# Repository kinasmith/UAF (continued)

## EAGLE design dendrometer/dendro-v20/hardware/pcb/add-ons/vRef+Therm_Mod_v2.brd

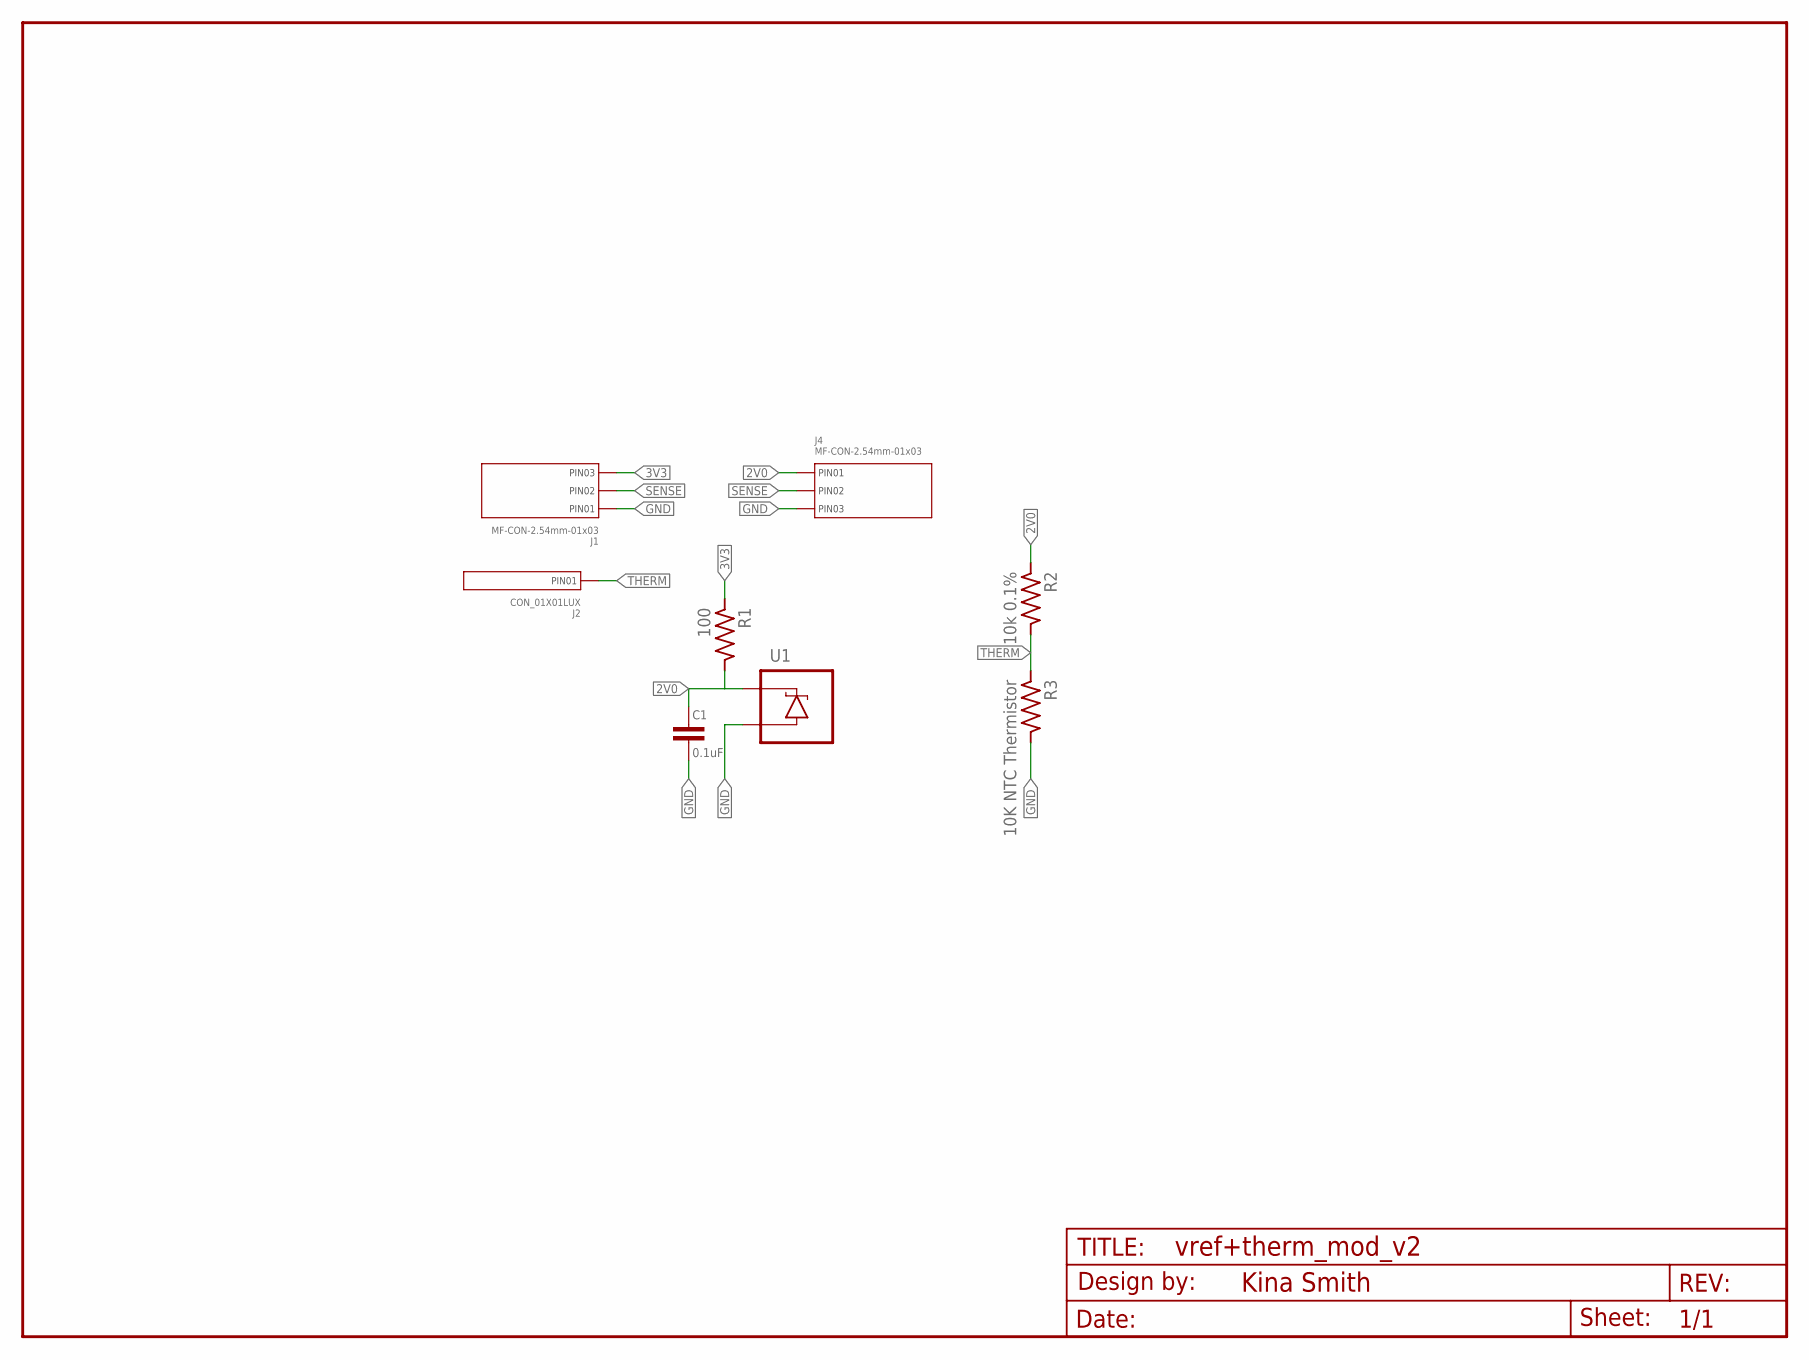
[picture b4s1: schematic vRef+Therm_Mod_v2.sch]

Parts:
C1: 0.1uF; C0603-N
FRAME1: FRAME-LETTERNO_PACKAGE; DUMMY
J1, J4: MF-CON-2.54mm-01x03; PTH_2.54MM_01X03
J2: CON_01X01LUX; 1X01_LUXEON-PAD
R1: 100; R0603-N
R2: 10k 0.1%; R0603-N
R3: 10K NTC Thermistor; R0603-N
U1: LM4040-SOT-23-3; SOT23-3

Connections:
2V0: C1.1, J4.P$1 (PIN1), R1.2, R2.1, U1.1 (C)
3V3: J1.P$3 (PIN3), R1.1
GND: C1.2, J1.P$1 (PIN1), J4.P$3 (PIN3), R3.2, U1.2 (A)
SENSE: J1.P$2 (PIN2), J4.P$2 (PIN2)
THERM: J2.P$1, R2.2, R3.1

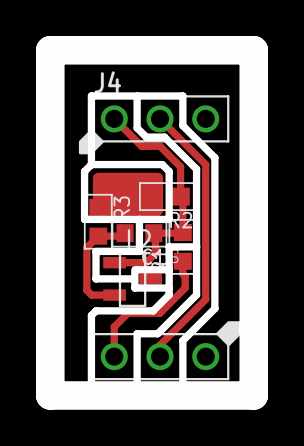
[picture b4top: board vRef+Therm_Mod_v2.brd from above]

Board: 2 copper layers, 11.3 x 19.2 mm, 9 parts (0 on the bottom side), 5 nets.

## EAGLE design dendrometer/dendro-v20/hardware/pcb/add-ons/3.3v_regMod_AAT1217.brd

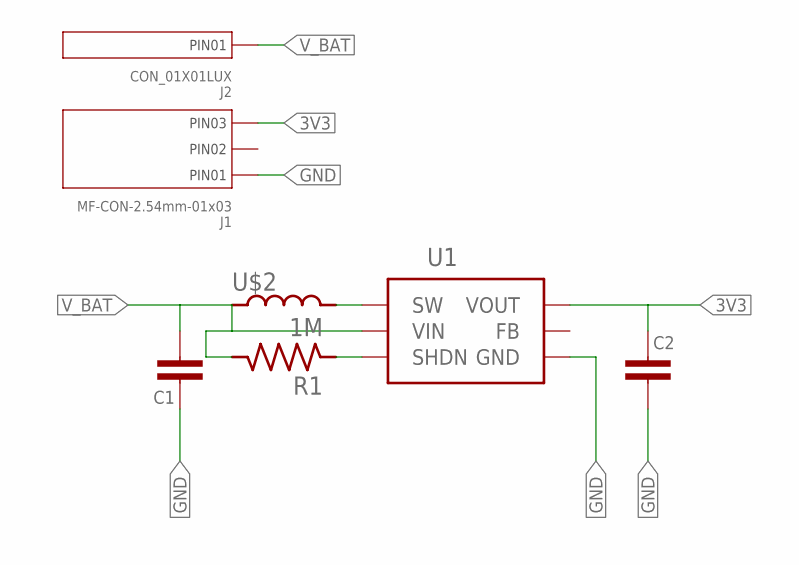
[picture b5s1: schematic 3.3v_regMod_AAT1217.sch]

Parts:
C1, C2: CAPACITOR_NP0603-N; C0603-N
J1: MF-CON-2.54mm-01x03; PTH_2.54MM_01X03
J2: CON_01X01LUX; 1X01_LUXEON-PAD
R1: 1M; R0603-N
U1: AAT1217-SOT23-6; SOT23-6
U$2: INDUCTOR3030; L3030

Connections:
3V3: C2.1, J1.P$3 (PIN3), U1.5 (VOUT)
GND: C1.1, C2.2, J1.P$1 (PIN1), U1.2 (GND)
unnamed: U1.1 (SW), U$2.P$2
unnamed: R1.1, U1.4 (SHDN)
V_BAT: C1.2, J2.P$1, R1.2, U1.6 (VIN), U$2.P$1

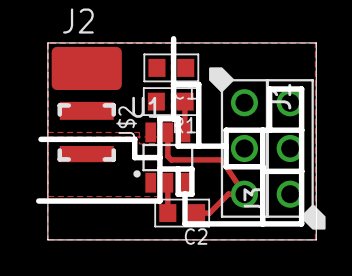
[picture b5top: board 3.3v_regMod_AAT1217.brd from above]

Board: 2 copper layers, 15.3 x 11.0 mm, 8 parts (0 on the bottom side), 5 nets.

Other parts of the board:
J3: MF-CON-2.54mm-01x03; PTH_2.54MM_01X03

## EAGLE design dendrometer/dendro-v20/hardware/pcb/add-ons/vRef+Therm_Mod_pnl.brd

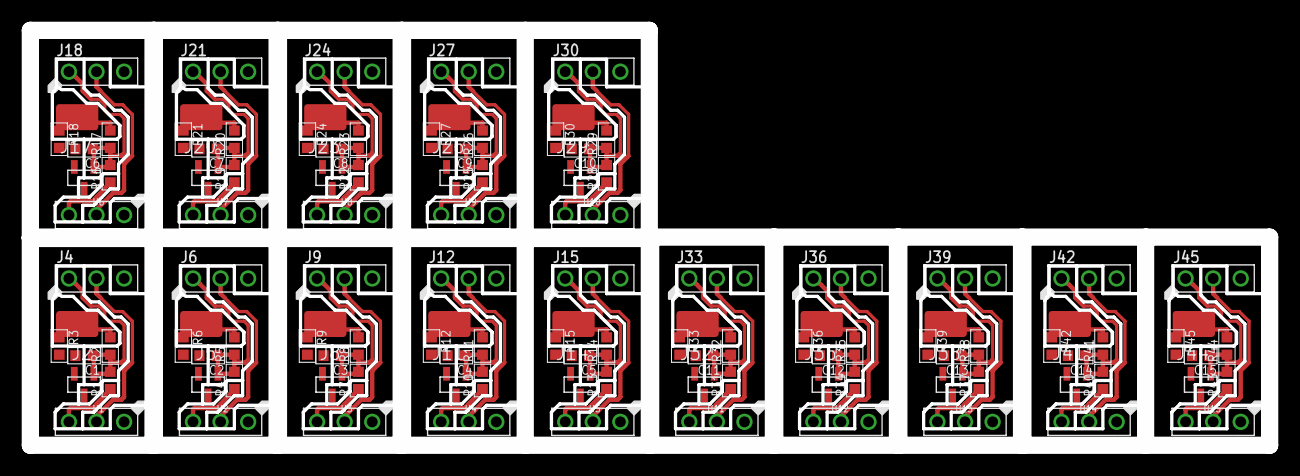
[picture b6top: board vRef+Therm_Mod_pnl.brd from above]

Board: 2 copper layers, 114.2 x 38.2 mm, 120 parts (0 on the bottom side), 75 nets.

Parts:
C1, C2, C3, C4, C5, C6, C7, C8, C9, C10, C11, C12, C13, C14, C15: 0.1uF; C0603-N
J1, J3, J4, J6, J7, J9, J10, J12, J13, J15, J16, J18, J19, J21, J22, J24, J25, J27, J28, J30, J31, J33, J34, J36, J37, J39, J40, J42, J43, J45: MF-CON-2.54mm-01x03; PTH_2.54MM_01X03
J2, J5, J8, J11, J14, J17, J20, J23, J26, J29, J32, J35, J38, J41, J44: CON_01X01LUX; 1X01_LUXEON-PAD
R1, R4, R7, R10, R13, R16, R19, R22, R25, R28, R31, R34, R37, R40, R43: 100; R0603-N
R2, R5, R8, R11, R14, R17, R20, R23, R26, R29, R32, R35, R38, R41, R44: 10k 0.1%; R0603-N
R3, R6, R9, R12, R15, R18, R21, R24, R27, R30, R33, R36, R39, R42, R45: 10K NTC Thermistor; R0603-N
U1, U2, U3, U4, U5, U6, U7, U8, U9, U10, U11, U12, U13, U14, U15: LM4040-SOT-23-3; SOT23-3

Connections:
2V0: C1.1, J4.P$1, R1.2, R2.1, U1.1
2V1: C2.1, J6.P$1, R4.2, R5.1, U2.1
2V2: C3.1, J9.P$1, R7.2, R8.1, U3.1
2V3: C4.1, J12.P$1, R10.2, R11.1, U4.1
2V4: C5.1, J15.P$1, R13.2, R14.1, U5.1
2V5: C6.1, J18.P$1, R16.2, R17.1, U6.1
2V6: C7.1, J21.P$1, R19.2, R20.1, U7.1
2V7: C8.1, J24.P$1, R22.2, R23.1, U8.1
2V8: C9.1, J27.P$1, R25.2, R26.1, U9.1
2V9: C10.1, J30.P$1, R28.2, R29.1, U10.1
2V10: C11.1, J33.P$1, R31.2, R32.1, U11.1
2V11: C12.1, J36.P$1, R34.2, R35.1, U12.1
2V12: C13.1, J39.P$1, R37.2, R38.1, U13.1
2V13: C14.1, J42.P$1, R40.2, R41.1, U14.1
2V14: C15.1, J45.P$1, R43.2, R44.1, U15.1
3V1: J3.P$3, R4.1
3V2: J7.P$3, R7.1
3V3: J1.P$3, R1.1
3V4: J10.P$3, R10.1
3V5: J13.P$3, R13.1
3V6: J16.P$3, R16.1
3V7: J19.P$3, R19.1
3V8: J22.P$3, R22.1
3V9: J25.P$3, R25.1
3V10: J28.P$3, R28.1
3V11: J31.P$3, R31.1
3V12: J34.P$3, R34.1
3V13: J37.P$3, R37.1
3V14: J40.P$3, R40.1
3V15: J43.P$3, R43.1
GND: C1.2, J1.P$1, J4.P$3, R3.2, U1.2
GND1: C2.2, J3.P$1, J6.P$3, R6.2, U2.2
GND2: C3.2, J7.P$1, J9.P$3, R9.2, U3.2
GND3: C4.2, J10.P$1, J12.P$3, R12.2, U4.2
GND4: C5.2, J13.P$1, J15.P$3, R15.2, U5.2
GND5: C6.2, J16.P$1, J18.P$3, R18.2, U6.2
GND6: C7.2, J19.P$1, J21.P$3, R21.2, U7.2
GND7: C8.2, J22.P$1, J24.P$3, R24.2, U8.2
GND8: C9.2, J25.P$1, J27.P$3, R27.2, U9.2
GND9: C10.2, J28.P$1, J30.P$3, R30.2, U10.2
GND10: C11.2, J31.P$1, J33.P$3, R33.2, U11.2
GND11: C12.2, J34.P$1, J36.P$3, R36.2, U12.2
GND12: C13.2, J37.P$1, J39.P$3, R39.2, U13.2
GND13: C14.2, J40.P$1, J42.P$3, R42.2, U14.2
GND14: C15.2, J43.P$1, J45.P$3, R45.2, U15.2
SENSE: J1.P$2, J4.P$2
SENSE1: J3.P$2, J6.P$2
SENSE2: J7.P$2, J9.P$2
SENSE3: J10.P$2, J12.P$2
SENSE4: J13.P$2, J15.P$2
SENSE5: J16.P$2, J18.P$2
SENSE6: J19.P$2, J21.P$2
SENSE7: J22.P$2, J24.P$2
SENSE8: J25.P$2, J27.P$2
SENSE9: J28.P$2, J30.P$2
SENSE10: J31.P$2, J33.P$2
SENSE11: J34.P$2, J36.P$2
SENSE12: J37.P$2, J39.P$2
SENSE13: J40.P$2, J42.P$2
SENSE14: J43.P$2, J45.P$2
THERM: J2.P$1, R2.2, R3.1
THERM1: J5.P$1, R5.2, R6.1
THERM2: J8.P$1, R8.2, R9.1
THERM3: J11.P$1, R11.2, R12.1
THERM4: J14.P$1, R14.2, R15.1
THERM5: J17.P$1, R17.2, R18.1
THERM6: J20.P$1, R20.2, R21.1
THERM7: J23.P$1, R23.2, R24.1
THERM8: J26.P$1, R26.2, R27.1
THERM9: J29.P$1, R29.2, R30.1
THERM10: J32.P$1, R32.2, R33.1
THERM11: J35.P$1, R35.2, R36.1
THERM12: J38.P$1, R38.2, R39.1
THERM13: J41.P$1, R41.2, R42.1
THERM14: J44.P$1, R44.2, R45.1

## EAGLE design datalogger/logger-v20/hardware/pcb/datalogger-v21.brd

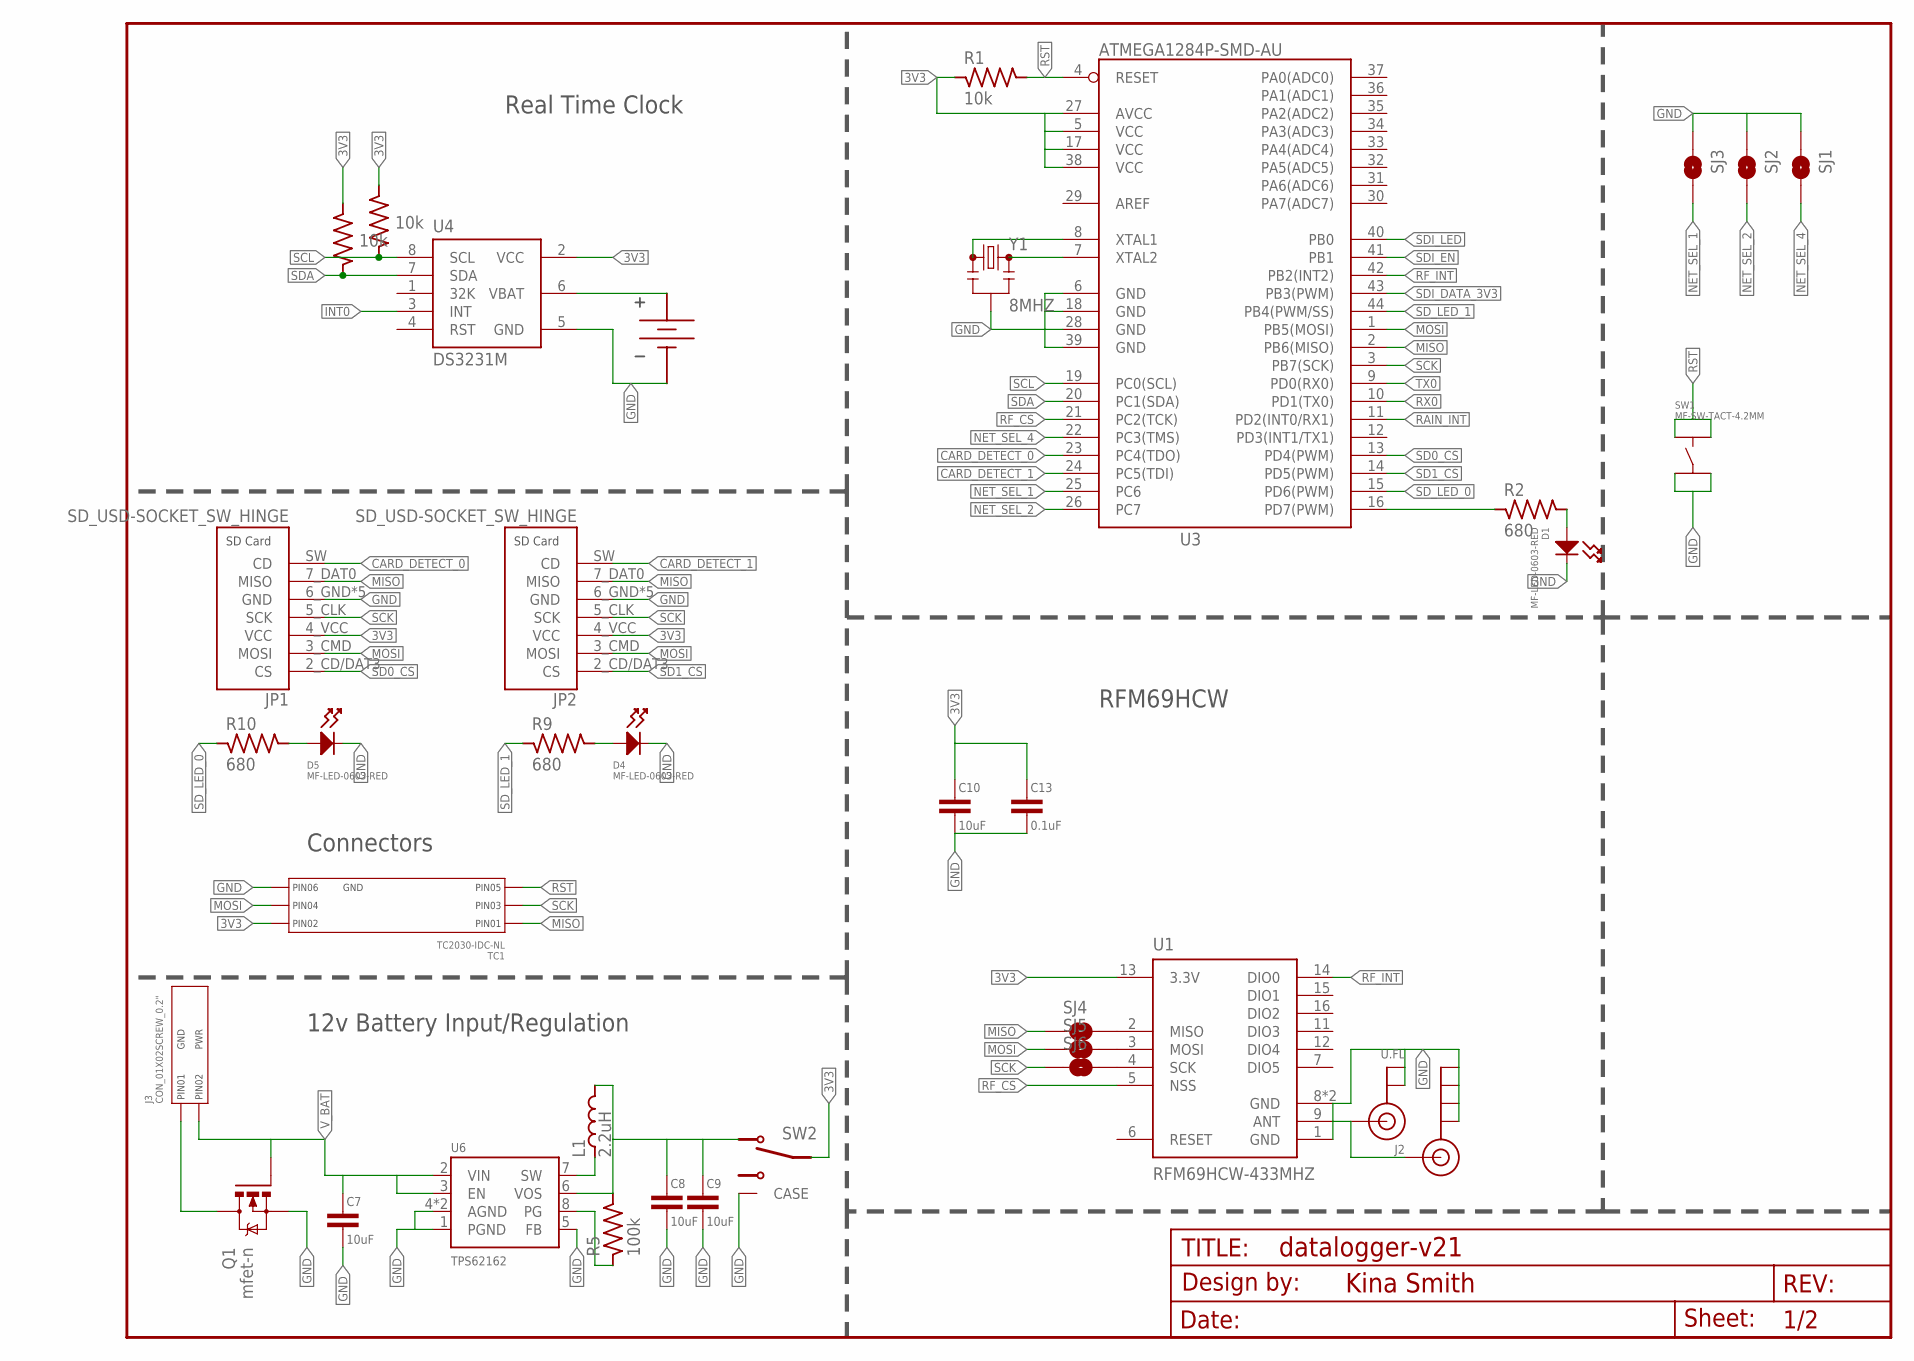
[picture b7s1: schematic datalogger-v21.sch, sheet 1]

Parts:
BAT1: BATTERY_HOLDER12MM; BAT_12MM
C7, C8, C9, C10: 10uF; C0805-N; PARTNO GRM21BR61C106KE15L
C13: 0.1uF; C0603-N; PARTNO CC0603KRX7R7BB104
D1, D4, D5: MF-LED-0603-RED; LED0603
FRAME1: FRAME-LETTERNO_PACKAGE; DUMMY
J2: U.FL; ADAFRUIT_U.FL
J3: CON_01X02SCREW_0.2"; SCREW_TERM_2POS
J4: ANTENNA_SMA_EDGE; SMA-EDGE
JP1, JP2: SD_USD-SOCKET_SW_HINGE; SD_MICRO_HIROSE-DM3C
L1: 2.2uH; L2520; PARTNO VLS252012T-2R2M1R3
Q1: mfet-n; SOT23-3; PARTNO SI2312BDS-T1-GE3
R1, R3, R4: 10k; R0603-N; PARTNO RC0603FR-0710KL
R2, R9, R10: 680; R0603-N; PARTNO RC0603FR-0710KL
R5: 100k; R0603-N; PARTNO RC0603FR-07100KL
SJ1, SJ2, SJ3, SJ4, SJ5, SJ6: JUMPER-PAD-2-NOYES_SILK; PAD-JUMPER-2-NO_YES_SILK
SW1: MF-SW-TACT-4.2MM; TACT4.2MM
SW2: SWITCH_SPDT_SMD_ES01MSABE; SPDT_ES01MSABE
TC1: TC2030-IDC-NL; PARTNO NA
U1: RFM69HCW-433MHZ; RFM69HCW-XXXS2
U3: ATMEGA1284P-SMD-AU; TQFP44
U4: DS3231M; SO08
U6: TPS62162; WSON-8
Y1: 8MHZ; RESONATOR-SMD

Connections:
3V3: C10.1, C13.1, JP1.4_VCC (VCC), JP2.4_VCC (VCC), R1.1, R3.2, R4.2, SW2.2 (COM), TC1.P$2 (PIN2), U1.13 (3.3V), U3.5 (VCC), U3.17 (VCC), U3.27 (AVCC), U3.38 (VCC), U4.2 (VCC); also elsewhere on the board
3V3_PRE: C8.1, C9.1, L1.P$2, R5.2, SW2.1, U6.6 (VOS); also elsewhere on the board
ANT: J2.3 (SIGNAL), J4.SIG (SIGNAL), U1.9 (ANT)
CARD_DETECT_0: JP1.SW (CD), U3.23 (PC4(TDO))
CARD_DETECT_1: JP2.SW (CD), U3.24 (PC5(TDI))
GND: BAT1.GND, C7.2, C8.2, C9.2, C10.2, C13.2, D1.CATHODE, D4.CATHODE, D5.CATHODE, J2.1 (GND), J2.2 (GND), J4.GND@0 (GND), J4.GND@1 (GND), J4.GND@2 (GND), J4.GND@3 (GND), JP1.6_GND (GND), JP1.GND1 (GND), JP1.GND2 (GND), JP1.GND3 (GND), JP1.GND4 (GND), JP2.6_GND (GND), JP2.GND1 (GND), JP2.GND2 (GND), JP2.GND3 (GND), JP2.GND4 (GND), Q1.2 (S), SJ1.1, SJ2.1, SJ3.1, SW1.P$3, SW1.P$4, SW2.GND (CASE), SW2.GND1 (CASE), TC1.P$6 (PIN6), U1.1 (GND), U1.8 (GND), U1.10 (GND), U3.6 (GND), U3.18 (GND), U3.28 (GND), U3.39 (GND), U4.5 (GND), U6.1 (PGND), U6.4 (AGND), U6.5 (FB), U6.P$9 (AGND), Y1.2; also elsewhere on the board
INT0: U4.3 (INT)
MISO: JP1.7_DAT0 (MISO), JP2.7_DAT0 (MISO), SJ4.1, TC1.P$1 (PIN1), U3.2 (PB6(MISO))
MOSI: JP1.3_CMD (MOSI), JP2.3_CMD (MOSI), SJ5.1, TC1.P$4 (PIN4), U3.1 (PB5(MOSI))
unnamed: J3.GND (PIN1), Q1.3 (D)
unnamed: R2.1, U3.16 (PD7(PWM))
unnamed: U3.7 (XTAL2), Y1.3
unnamed: D4.ANODE, R9.2
unnamed: U3.8 (XTAL1), Y1.1
unnamed: L1.P$1, U6.7 (SW)
unnamed: SJ4.2, U1.2 (MISO)
unnamed: D1.ANODE, R2.2
unnamed: SJ5.2, U1.3 (MOSI)
unnamed: BAT1.PWR@1 (VBAT), BAT1.PWR@2 (VBAT), U4.6 (VBAT)
unnamed: R5.1, U6.8 (PG)
unnamed: SJ6.2, U1.4 (SCK)
unnamed: D5.ANODE, R10.2
NET_SEL_1: SJ3.2, U3.25 (PC6)
NET_SEL_2: SJ2.2, U3.26 (PC7)
NET_SEL_4: SJ1.2, U3.22 (PC3(TMS))
RAIN_INT: U3.11 (PD2(INT0/RX1)); also elsewhere on the board
RF_CS: U1.5 (NSS), U3.21 (PC2(TCK))
RF_INT: U1.14 (DIO0), U3.42 (PB2(INT2))
RST: R1.2, SW1.P$1, SW1.P$2, TC1.P$5 (PIN5), U3.4 (RESET); also elsewhere on the board
RX0: U3.10 (PD1(TX0)); also elsewhere on the board
SCK: JP1.5_CLK (SCK), JP2.5_CLK (SCK), SJ6.1, TC1.P$3 (PIN3), U3.3 (PB7(SCK))
SCL: R3.1, U3.19 (PC0(SCL)), U4.8 (SCL)
SD0_CS: JP1.2_CD/DAT3 (CS), U3.13 (PD4(PWM))
SD1_CS: JP2.2_CD/DAT3 (CS), U3.14 (PD5(PWM))
SDA: R4.1, U3.20 (PC1(SDA)), U4.7 (SDA)
SDI_DATA_3V3: U3.43 (PB3(PWM)); also elsewhere on the board
SDI_EN: U3.41 (PB1); also elsewhere on the board
SDI_LED: U3.40 (PB0); also elsewhere on the board
SD_LED_0: R10.1, U3.15 (PD6(PWM))
SD_LED_1: R9.1, U3.44 (PB4(PWM/SS))
TX0: U3.9 (PD0(RX0)); also elsewhere on the board
V_BAT: C7.1, J3.PWR (PIN2), Q1.1 (G), U6.2 (VIN), U6.3 (EN); also elsewhere on the board

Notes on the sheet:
12v Battery Input/Regulation
RFM69HCW
Connectors
Real Time Clock

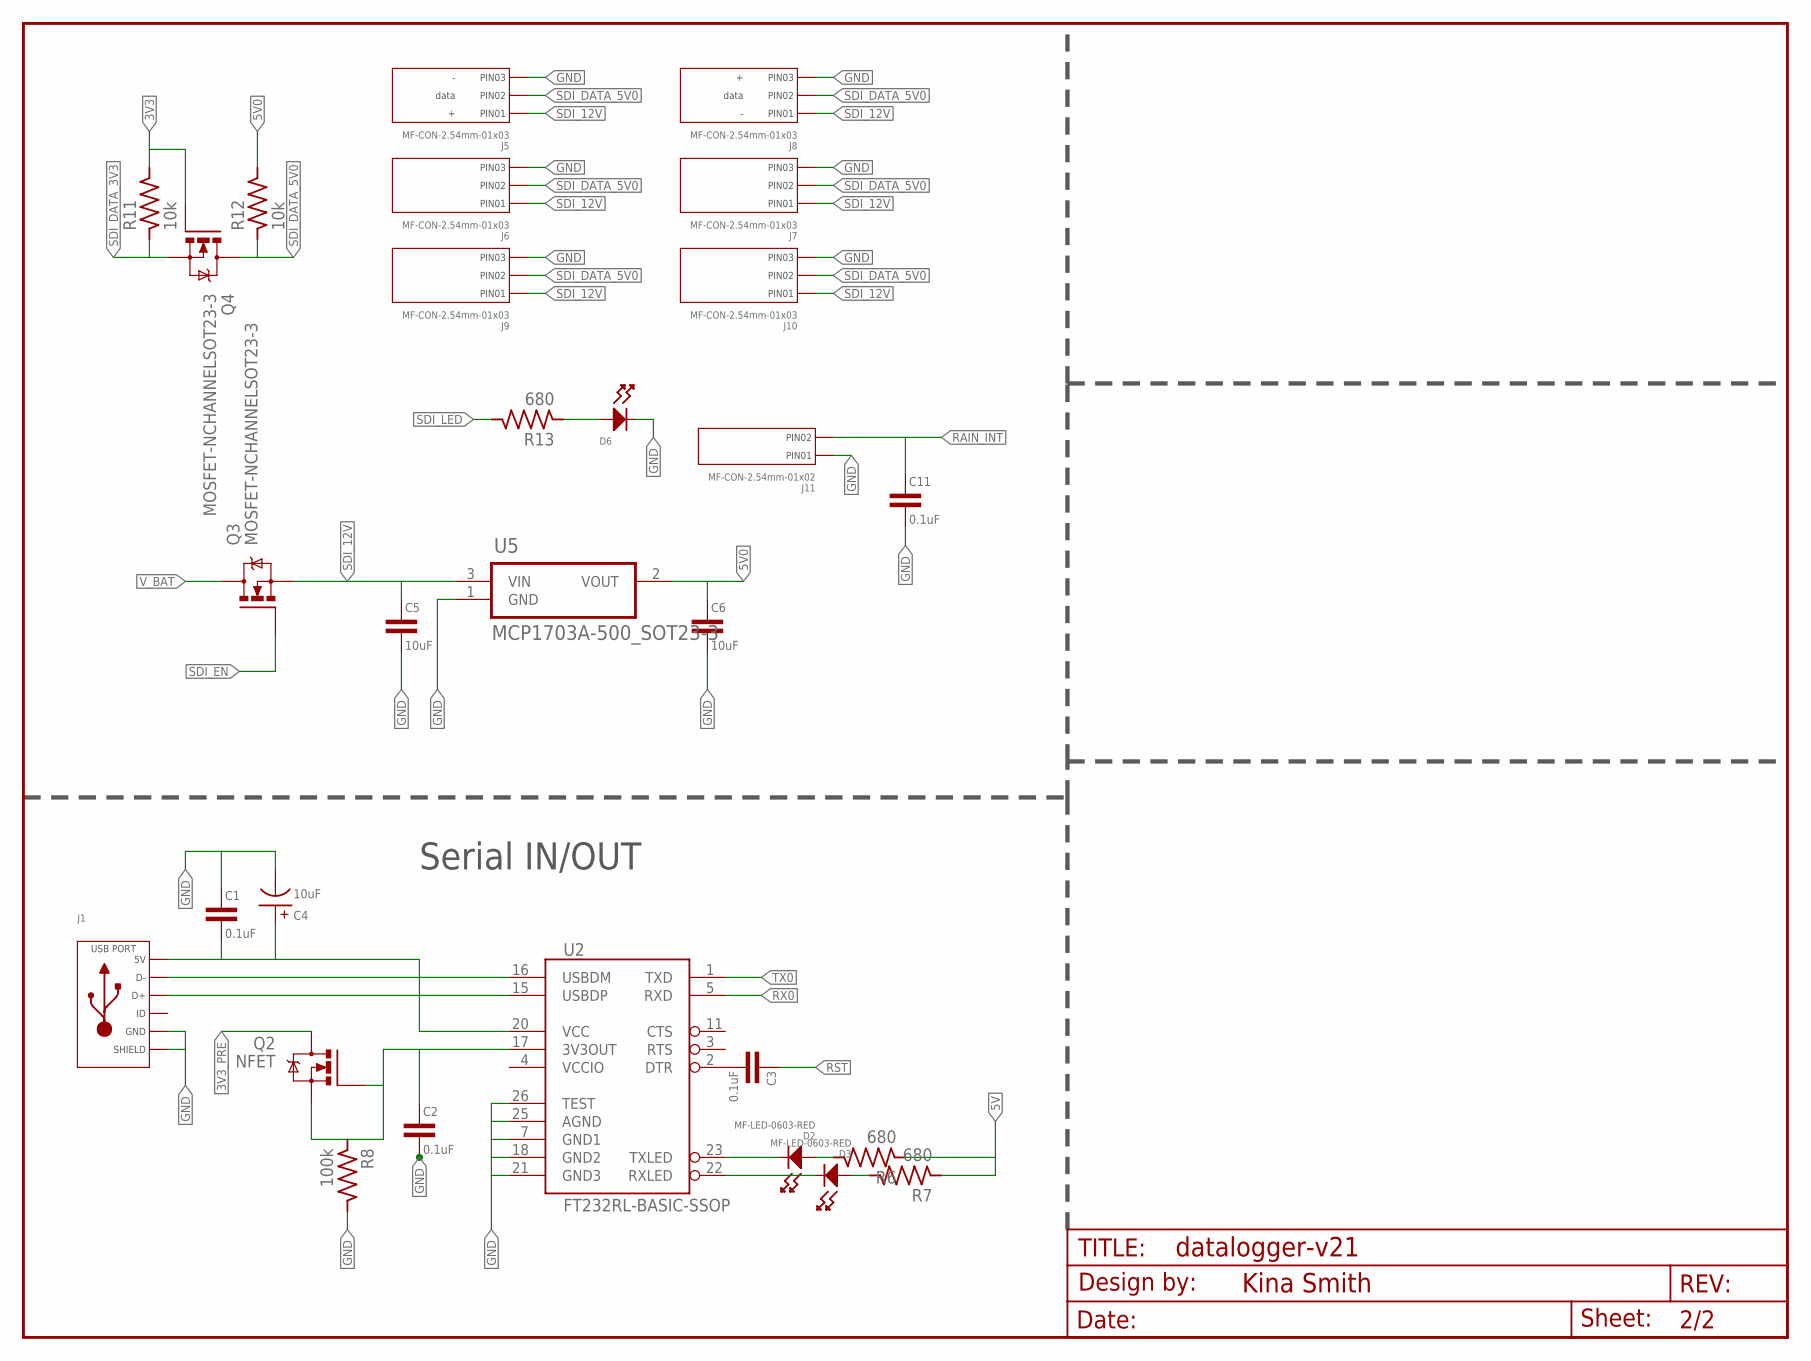
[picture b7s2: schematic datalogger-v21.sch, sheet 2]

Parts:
C1, C2, C3, C11: 0.1uF; C0603-N
C4: 10uF; EIA3216
C5, C6: 10uF; C0805-N
D2, D3: MF-LED-0603-RED; LED0603
D6: LED_SINGLE-0603; LED0603
FRAME3: FRAME-LETTERNO_PACKAGE; DUMMY
J1: USB-5PIN_B-MICRO_R/A_STRONG; USB-MICRO-MOLEX-105017-0001
J5, J6, J7, J8, J9, J10: MF-CON-2.54mm-01x03; PTH_2.54MM_01X03
J11: MF-CON-2.54mm-01x02; PTH_2.54MM_01X02
Q2: NFET; SOT23-3
Q3, Q4: MOSFET-NCHANNELSOT23-3; SOT23-3
R6, R7, R13: 680; R0603-N
R8: 100k; R0603-N
R11, R12: 10k; R0603-N
U2: FT232RL-BASIC-SSOP; SSOP28
U5: MCP1703A-500_SOT23-3; SOT23-3

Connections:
3V3: Q4.1 (G), R11.2; also elsewhere on the board
3V3_PRE: Q2.3 (D); also elsewhere on the board
5V: C1.2, C4.A (POS), J1.1 (5V), R6.1, R7.1, U2.20 (VCC)
5V0: C6.1, R12.2, U5.2 (VOUT)
GND: C1.1, C2.2, C4.C (NEG), C5.2, C6.2, C11.2, D6.CATHODE, J1.5 (GND), J1.P$1 (SLD), J1.P$2 (SLD), J1.P$3 (SLD), J1.P$4 (SLD), J1.P$5 (SLD), J1.P$6 (SLD), J5.P$3 (PIN3), J6.P$3 (PIN3), J7.P$3 (PIN3), J8.P$3 (PIN3), J9.P$3 (PIN3), J10.P$3 (PIN3), J11.P$1 (PIN1), R8.2, U2.7 (GND1), U2.18 (GND2), U2.21 (GND3), U2.25 (AGND), U2.26 (TEST), U5.1 (GND); also elsewhere on the board
unnamed: J1.2 (D-), U2.16 (USBDM)
unnamed: J1.3 (D+), U2.15 (USBDP)
unnamed: D6.ANODE, R13.1
unnamed: C2.1, Q2.1 (G), Q2.2 (S), R8.1, U2.17 (3V3OUT)
unnamed: C3.2, U2.2 (DTR)
unnamed: D2.CATHODE, U2.23 (TXLED)
unnamed: D3.CATHODE, U2.22 (RXLED)
unnamed: D3.ANODE, R7.2
unnamed: D2.ANODE, R6.2
RAIN_INT: C11.1, J11.P$2 (PIN2); also elsewhere on the board
RST: C3.1; also elsewhere on the board
RX0: U2.5 (RXD); also elsewhere on the board
SDI_12V: C5.1, J5.P$1 (PIN1), J6.P$1 (PIN1), J7.P$1 (PIN1), J8.P$1 (PIN1), J9.P$1 (PIN1), J10.P$1 (PIN1), Q3.2 (S), U5.3 (VIN)
SDI_DATA_3V3: Q4.2 (S), R11.1; also elsewhere on the board
SDI_DATA_5V0: J5.P$2 (PIN2), J6.P$2 (PIN2), J7.P$2 (PIN2), J8.P$2 (PIN2), J9.P$2 (PIN2), J10.P$2 (PIN2), Q4.3 (D), R12.1
SDI_EN: Q3.1 (G); also elsewhere on the board
SDI_LED: R13.2; also elsewhere on the board
TX0: U2.1 (TXD); also elsewhere on the board
VCCIO: U2.4 (VCCIO)
V_BAT: Q3.3 (D); also elsewhere on the board

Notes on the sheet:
Serial IN/OUT

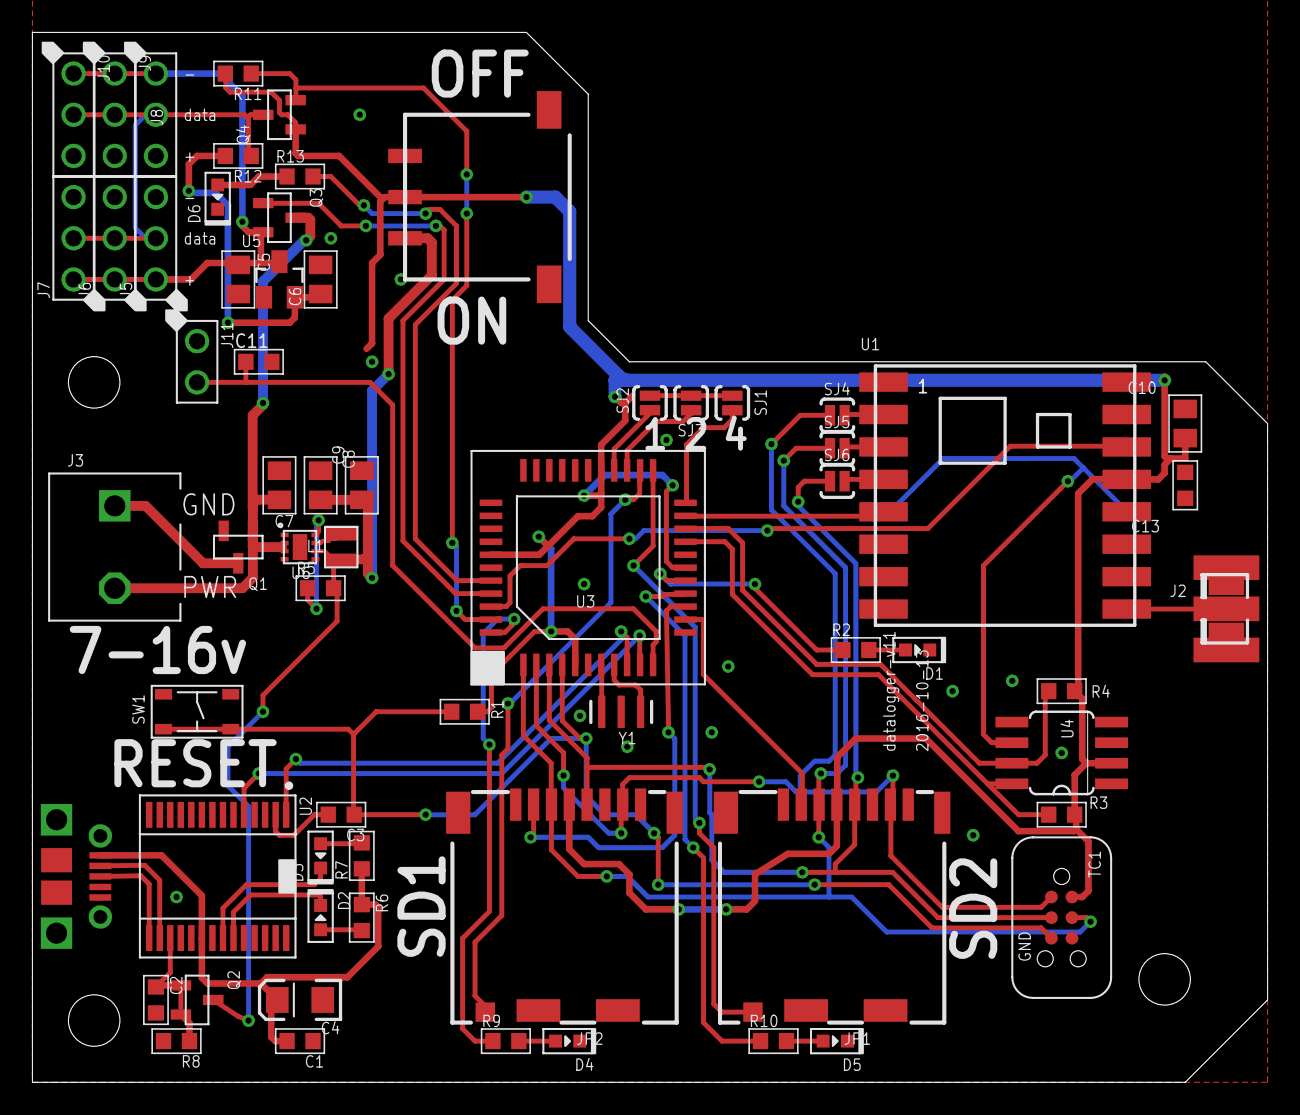
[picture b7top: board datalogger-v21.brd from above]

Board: 2 copper layers, 76.2 x 64.8 mm, 68 parts (1 on the bottom side), 54 nets.

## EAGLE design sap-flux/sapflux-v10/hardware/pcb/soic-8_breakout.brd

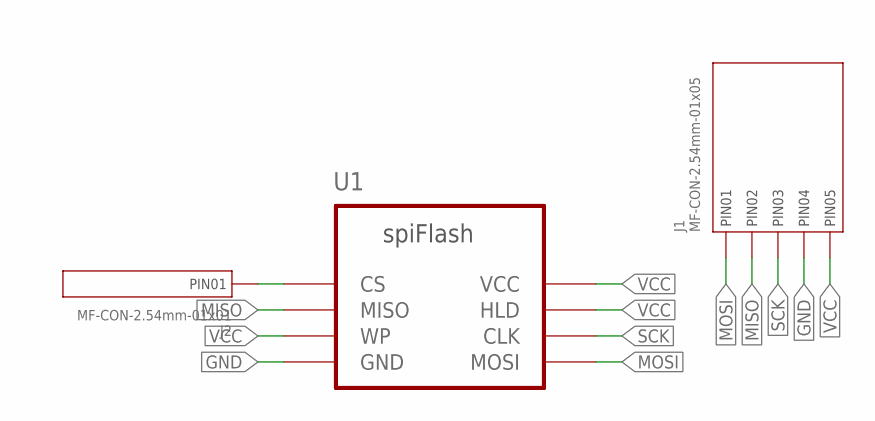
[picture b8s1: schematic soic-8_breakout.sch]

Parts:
J1: MF-CON-2.54mm-01x05; PTH_2.54MM_01X05
J2: MF-CON-2.54mm-01x01; PTH_2.54MM_01X01
U1: WINBOND_FLASH_4MBIT-SOIC; SOIC8

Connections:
GND: J1.P$4 (PIN4), U1.4 (GND)
MISO: J1.P$2 (PIN2), U1.2 (MISO)
MOSI: J1.P$1 (PIN1), U1.5 (MOSI)
unnamed: J2.P$1, U1.1 (CS)
SCK: J1.P$3 (PIN3), U1.6 (CLK)
VCC: J1.P$5 (PIN5), U1.3 (WP), U1.7 (HLD), U1.8 (VCC)

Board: 2 copper layers, 3 parts (0 on the bottom side), 6 nets, no tracks yet.

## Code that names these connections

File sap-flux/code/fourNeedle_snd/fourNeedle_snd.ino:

/*
   Tc 1: CSpin 9
   Tc 2: CSpin 8
   Tc 3: CSpin 7
   Tc Heat: CSpin 6
   H_en: pin 5
*/

#include <SPI.h>
#include "RFM69.h"
#include "Adafruit_MAX31855.h"

#define NODE_ID         2
#define NETWORK_ID      105
#define GATEWAY_ID      0
#define FREQUENCY       RF69_433MHZ
#define KEY             "p6ZNvTmGfdY2hUXb" //has to be same 16 characters/bytes on all nodes, not more not less!
#define ACK_TIME        100  // # of ms to wait for an ack
#define NB_ATTEMPTS_ACK 5 //number of attempts to try before giving up

#define Tc1_CS 9
#define Tc2_CS 8
#define Tc3_CS 7
#define TcH_CS 6
#define H_en 5

Adafruit_MAX31855 Tc1(Tc1_CS);
Adafruit_MAX31855 Tc2(Tc2_CS);
Adafruit_MAX31855 Tc3(Tc3_CS);
Adafruit_MAX31855 TcH(TcH_CS);
RFM69 radio;

long TRANSMIT_PERIOD = 30000; //transmit a packet to gateway so often (in ms)
int TRANSMIT_PERIOD_MINUTES = 1;
int ACK_FAIL_WAIT_PERIOD = 500;


long currentTime;
long h_saved_time;
long h_interval;
const long h_pulse_on = 6000;
const long h_pulse_off = 30 * 60000;
//const long h_pulse_off = 60000;
int h_status = 1;

long log_saved_time;
int log_interval = 6000;

typedef struct {
  int node_id;
  float Tc1_t;
  float Tc2_t;
  float Tc3_t;
  float TcH_t;
}
Payload;
Payload payload;

void setup() {
  Serial.begin(9600);
  pinMode(H_en, OUTPUT);
  digitalWrite(H_en, LOW);
payload.node_id = NODE_ID;
  radio.initialize(FREQUENCY, NODE_ID, NETWORK_ID); //Begin Radio
  radio.setHighPower(); //uncomment only for RFM69HW!
  radio.encrypt(KEY); //Encrypt
  radio.sleep(); //Sleep radio (saves power)
  char buff[50];
  sprintf(buff, "Listening at %d Mhz...", FREQUENCY == RF69_433MHZ ? 433 : FREQUENCY == RF69_868MHZ ? 868 : 915);
}

void loop() {
  currentTime = millis();
  if (h_saved_time + h_interval < currentTime) {
    //if heater is on, wait 6 seconds
    if (h_status == 1) {
      digitalWrite(H_en, HIGH);
      h_interval = h_pulse_on;
      h_status = 0; //set status for next round.
      Serial.print("Heat interval ");
      Serial.print(h_pulse_on / 1000);
      Serial.println("s");
    }
    else if (h_status == 0) {
      digitalWrite(H_en, LOW);
      h_interval = h_pulse_off;
      h_status = 1; //set status for next round
      Serial.print("Heat interval ");
      Serial.print(h_pulse_off / 1000);
      Serial.println("s");
    }
    h_saved_time = currentTime;
  }
  if (log_saved_time + log_interval < currentTime) {
    payload.Tc1_t = Tc1.readCelsius();
    payload.Tc2_t = Tc2.readCelsius();
    payload.Tc3_t = Tc3.readCelsius();
    payload.TcH_t = TcH.readCelsius();
    sendPacket();
    printPacket();
    log_saved_time = currentTime;
  }
}

void sendPacket() {
  int nAttempt = 0; 
  bool flag_ACK_received = false;
  while (nAttempt < NB_ATTEMPTS_ACK && !flag_ACK_received) { 
    if (radio.sendWithRetry(GATEWAY_ID, (const void*)(&payload), sizeof(payload))) { 
      flag_ACK_received = true;
    }
    else { 
      if (radio.sendWithRetry(GATEWAY_ID, (const void*)(&payload), sizeof(payload))) {
        flag_ACK_received = true; 
      }
      nAttempt++;
      ACK_FAIL_WAIT_PERIOD = random(300, 600);
      delay(ACK_FAIL_WAIT_PERIOD);
    }
  }
}
void printPacket() {
  Serial.print(payload.Tc1_t);
  Serial.print(", ");
  Serial.print(payload.Tc2_t);
  Serial.print(", ");
  Serial.print(payload.Tc3_t);
  Serial.print(", ");
  Serial.print(payload.TcH_t);
  Serial.println();
}

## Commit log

2016-03-07 added ignore file
2016-03-07 global .gitignore didn't work..hmm
2016-03-07 added folders and BOM's
2016-03-07 moved stuff around, ready to work
2016-03-07 added libraries folder
2016-03-07 added project timeline
2016-03-08 added datasheets, ds3231 breakout pcb, got test code for senders and receiver. test writing to SD card overnight to test stability.
2016-03-09 started the mechanical design in SLDWRKS
2016-03-09 changed the test sketches. Recording tempreading from RFM69 radio and bat. voltage. Initiating longer term test. Also data from overnight random number test
2016-03-09 added bolt tabs to dendrometer housing.
2016-03-10 did some more stuff to the solidworks files...I forgot what
2016-03-16 moved SD card write to correct place in code to fix double writes
2016-03-16 did some minor pcb work and did some data analysis
2016-03-16 changed where it was writing to SD card. Fixed duplicate writes
2016-04-05 I've been way behind. Here is a shitload of stuff. Status is, everything is working pretty darn well right now
2016-04-07 made .brd for pcb fab house. and other minor code changes
2016-04-13 generated gerber files and did some minor mech. work
2016-04-15 did minor stuff mostly. However created Reciever_0 and added SD card checking
2016-04-29 bunch of shit. oops
2016-06-13 ....long time. bunch of stuff...oops
2016-06-13 added debug Serial Print logic, modified the RTC library on RCV.
2016-06-13 switched to SDfat library and changed the SD fail interaction
2016-06-13 staged for deployment
2016-06-13 final upload...
2016-07-21 cleanup..
2016-08-23 massive move and restructure
2016-08-23 move in of all other projects
2016-08-23 dummy...wtf electron
2016-08-23 added electron folder to ignore
2016-08-23 moved welder files into subdir
2016-08-24 minor code updates...
2016-08-24 updated Sender_ and removed Serial.prints
2016-08-25 changed some things
2016-09-07 added particle stuff and made a breakout for rfm69hcw
2016-09-08 test data and new breakout board for themocouple amp
2016-09-08 changed
2016-09-30 crazy long time since I did this. hah
2016-10-10 added datasheets, test data, etc
2016-10-10 datalogger pcb design
2016-11-09 again....this is stupid
2016-11-11 two way communication. time stamp to sndr boards. and flow chart
2016-11-11 local data storage. auto send backed up data. And it works
2016-11-19 working on storing/transmitting data from sensors. Might have a working system by moving all send events out of the receive event. Needs further testing.
2016-11-23 Sap Flux Schematic. New parts in Eagle Libs. Block Diagram of Sap Flux system
2016-12-13 sap flux BOM, Gerbers, Radiation Shield Files
2016-12-14 removed optiboot
2016-12-28 started Dendro-v60
2017-01-03 massive shift. Moving to PlatformIO as an IDE
2017-01-03 testing git plugin
2017-01-03 changed formatting slightly.
2017-01-18 new circuit board. testing components
2017-01-18 battery voltage working...something weird with it now though
2017-01-18 something wrong with the SPI Bus
2017-01-19 spiflash memory
2017-01-19 Flash AND Radio works!
2017-01-20 talking to radio and flash mem. Need more testing for data storage and retrieval, but in testing it works to manually save/delete/retrieve data
2017-01-20 code variant for Sap Flux system with small v11 datalogger board
2017-01-20 cleanup
2017-01-20 added a junk folder
2017-01-20 working on flash mem. Try simple examples on how to save data repeatedly in the same locations
2017-01-24 flash mem. storage is working. Next steps: routines for flux measurements
2017-01-24 flash works with this code....going to move in sensor reading blocks
2017-01-24 also everything is FUCKED
2017-01-24 everything is STILL FUCKED
2017-01-25 still not fucked
2017-01-25 trying something that will FUCK IT UP
2017-01-25 not fucked yet
2017-01-25 not fucked....what the fuck
2017-01-25 this fucked everything
2017-01-25 FUCKING WORKS
2017-01-25 Fucked again
2017-01-25 things are working like a charm. Next, figure out how to seperate data chunks when re-transmitting
2017-01-25 changed payload uint16_t's to doubles to allow for Floats
2017-01-25 working for the most part, for now
2017-01-25 minor tweak for saving values.
2017-01-26 made datalogger latching
2017-01-26 logger now latches to sensor during data transmission. Needs testing
2017-01-30 Kind of fucked up the libraries and no things are not responding due to new MAX31856 Library
2017-01-30 MAX31856 library works, but now Flash is broken
2017-01-30 changed library thingy
2017-01-30 testing my MAX31856 Library
2017-01-31 works, but only when reset without the FTDI installed
2017-01-31 over night test
2017-01-31 Got the correct time stamp behavior working with reading back storage data
2017-01-31 just set the time and commented out the TIME SETTING thing
2017-01-31 minor stuff for overnight test
2017-01-31 nothing
2017-01-31 fixed readme
2017-02-03 added test data
2017-02-03 Data from field site. and worked on pcb slightly
2017-02-07 working on updating code and building add-on mods for system
2017-02-07 new dendro datalogger code. Based off home automation, and sap flux dev
2017-02-07 just nothing
2017-02-07 forgot to save
2017-02-07 starting power testing
2017-02-07 did power calculations
2017-02-08 final for test
2017-02-08 new data from overnight test
2017-02-09 zipped Data from field sites
2017-02-09 checked all part numbers. Minor modifications to bottom text layer
2017-02-10 created Gerbers
2017-02-10 new test data
2017-02-10 updated bottom Silk Screen
2017-02-11 serial log from overnight test. also notes for debuggin
2017-02-15 testing SDI-12 and Interrupt Rain Bucket. + new Data
2017-02-16 rebuilt model. Tightened tolerances for fit. etc
2017-02-16 made new gerbers including drill file
2017-02-17 changed power Testing code for testing new module
2017-02-17 fixed timing bug and reformed the comms structure so it makes more sense
2017-02-17 added a ping function and tided up some stuff
2017-02-20 fixed initial ping in Setup. ++new data
2017-02-21 small changes to datalogger
2017-02-28 added data
2017-02-28 making add-on boards for dendro upgrades)
2017-03-01 updated dendro logger code. fixed the latch ID variable type. was int changed to uint
2017-03-01 updating
2017-03-02 getting the dendro's ready to go
2017-03-02 more data
2017-03-03 more test data, more tweaking the Dendros
2017-03-06 more test data
2017-03-06 targeted upload
2017-03-06 trying figure out inverted temperatures
2017-03-06 testing 101 network. Added new batteries, and 10ms wait time to temp. readings
2017-03-07 labeled the thermocouple connections
2017-03-07 I think I fixed the timing issue with sending stored eeprom data
2017-03-07 made serial prints more concise
2017-03-08 testing thermocouple stability
2017-03-09 trying to figure out thermocouple cold junction issue
2017-03-09 testinggit add dendrometer/
2017-03-09 made case for datalogger
2017-03-10 case finished
2017-03-10 final upload of code
2017-03-10 more testing
2017-03-11 more tc-testing
2017-03-15 random data stuff
2017-03-15 vRef Testing
2017-04-11 testing with datalogger shield
2017-04-11 testing new code for Vref monitoring
2017-04-11 routing heater isolation
2017-04-11 added reference voltage recording to main datalogger code
2017-04-11 changed timing of reference voltage reads
2017-04-13 wire.begin not declared
2017-04-13 more data and minor timing for sensor readings
2017-04-13 junk
2017-04-13 cleaned up
2017-04-14 commenting dendro
2017-04-14 editing comments
2017-04-19 Radio comms not working. Single bytes will transmit for handshakes, timestamps. But Structs don't transfer anymore.
2017-04-19 finally get Sap Flux Working. It was a Bad Radio that was causing issues
2017-04-20 All working. Doing a Test tonight
2017-04-21 ping timeouts
2017-04-21 trying to figure out why it's dying. Figured it out. Trace going to Battery and 3.3v reg not big enough. Lots of power noise. Soldered more wires and more capacitors fixed the issue. Updated eagle sc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
2017-04-21 Just tidying up and setting timing intervals back to nrmal for a overnight test
2017-04-21 testing data
2017-04-24 More Data && Added radio and Tc Amp initialization for every read cycle
2017-04-28 more data and more junk
2017-04-29 at version 1. everything seems to work ok
2017-05-07 minor changes to fade out and fade times
2017-05-07 new drill jig
2017-05-09 bug in the TimeStamp functions. converted all times to Seconds
2017-05-09 added note about R script for converting UTC timestamp
2017-05-09 pushed code to devices
2017-05-09 testing with Moteino
2017-05-10 another bug involving intervals rolling over Should be fixed
2018-05-10 Backlink to CADLAB.io has been added.
